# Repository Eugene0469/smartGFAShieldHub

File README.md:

# SmartGFA_hubBoard
This is a design of a sensor hub to connect the hat board to the sensors and rf board.

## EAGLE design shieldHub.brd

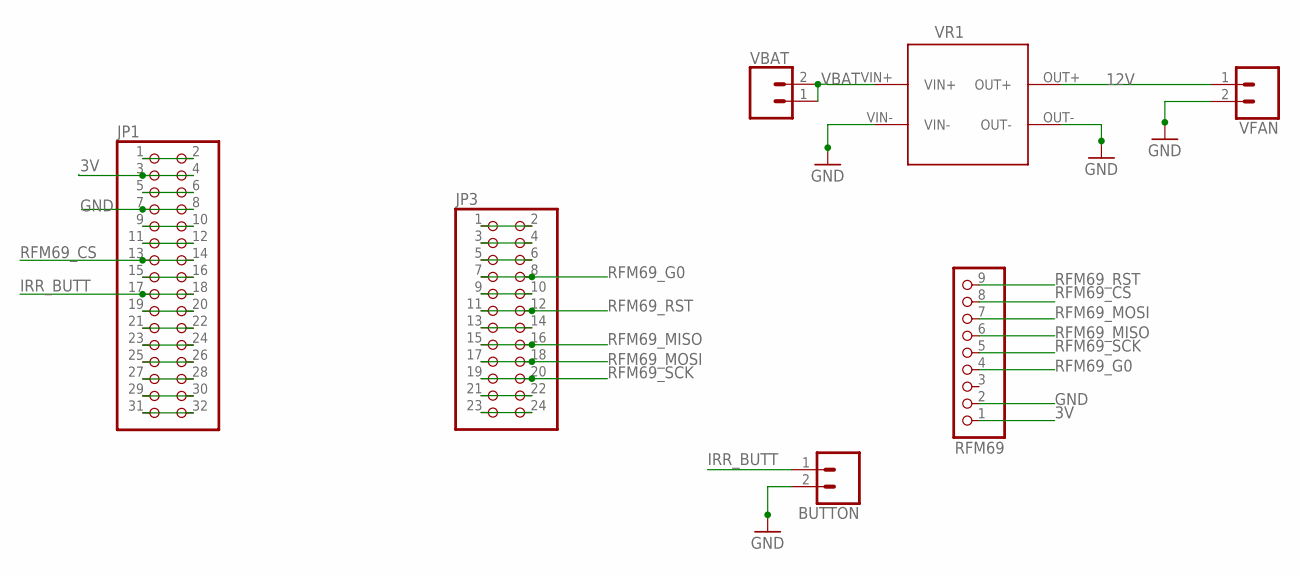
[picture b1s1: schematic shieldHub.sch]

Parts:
BUTTON: CONN_023.5MM_LOCK; SCREWTERMINAL-3.5MM-2_LOCK
JP1: PINHD-2X16; 2X16
JP3: PINHD-2X12; 2X12
RFM69: PINHD-1X9; 1X09-BIG
VBAT: CONN_02; 1X02
VFAN: CONN_023.5MM_LOCK; SCREWTERMINAL-3.5MM-2_LOCK
VR1: MT3608THROUGH_HOLE; MT3608

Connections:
3V: JP1.3, JP1.4, RFM69.1
12V: VFAN.1, VR1.OUT+
GND: BUTTON.2, JP1.7, JP1.8, RFM69.2, VFAN.2, VR1.OUT-, VR1.VIN-
IRR_BUTT: BUTTON.1, JP1.17, JP1.18
unnamed: JP1.1, JP1.2
unnamed: JP1.5, JP1.6
unnamed: JP1.9, JP1.10
unnamed: JP1.11, JP1.12
unnamed: JP3.23, JP3.24
unnamed: JP1.15, JP1.16
unnamed: JP1.19, JP1.20
unnamed: JP1.21, JP1.22
unnamed: JP1.23, JP1.24
unnamed: JP1.25, JP1.26
unnamed: JP3.21, JP3.22
unnamed: JP1.31, JP1.32
unnamed: JP3.13, JP3.14
unnamed: JP3.9, JP3.10
unnamed: JP3.5, JP3.6
unnamed: JP3.3, JP3.4
unnamed: JP3.1, JP3.2
RFM69_CS: JP1.13, JP1.14, RFM69.8
RFM69_G0: JP3.7, JP3.8, RFM69.4
RFM69_MISO: JP3.15, JP3.16, RFM69.6
RFM69_MOSI: JP3.17, JP3.18, RFM69.7
RFM69_RST: JP3.11, JP3.12, RFM69.9
RFM69_SCK: JP3.19, JP3.20, RFM69.5
RX: JP1.27, JP1.28
TX: JP1.29, JP1.30
VBAT: VBAT.1, VBAT.2, VR1.VIN+

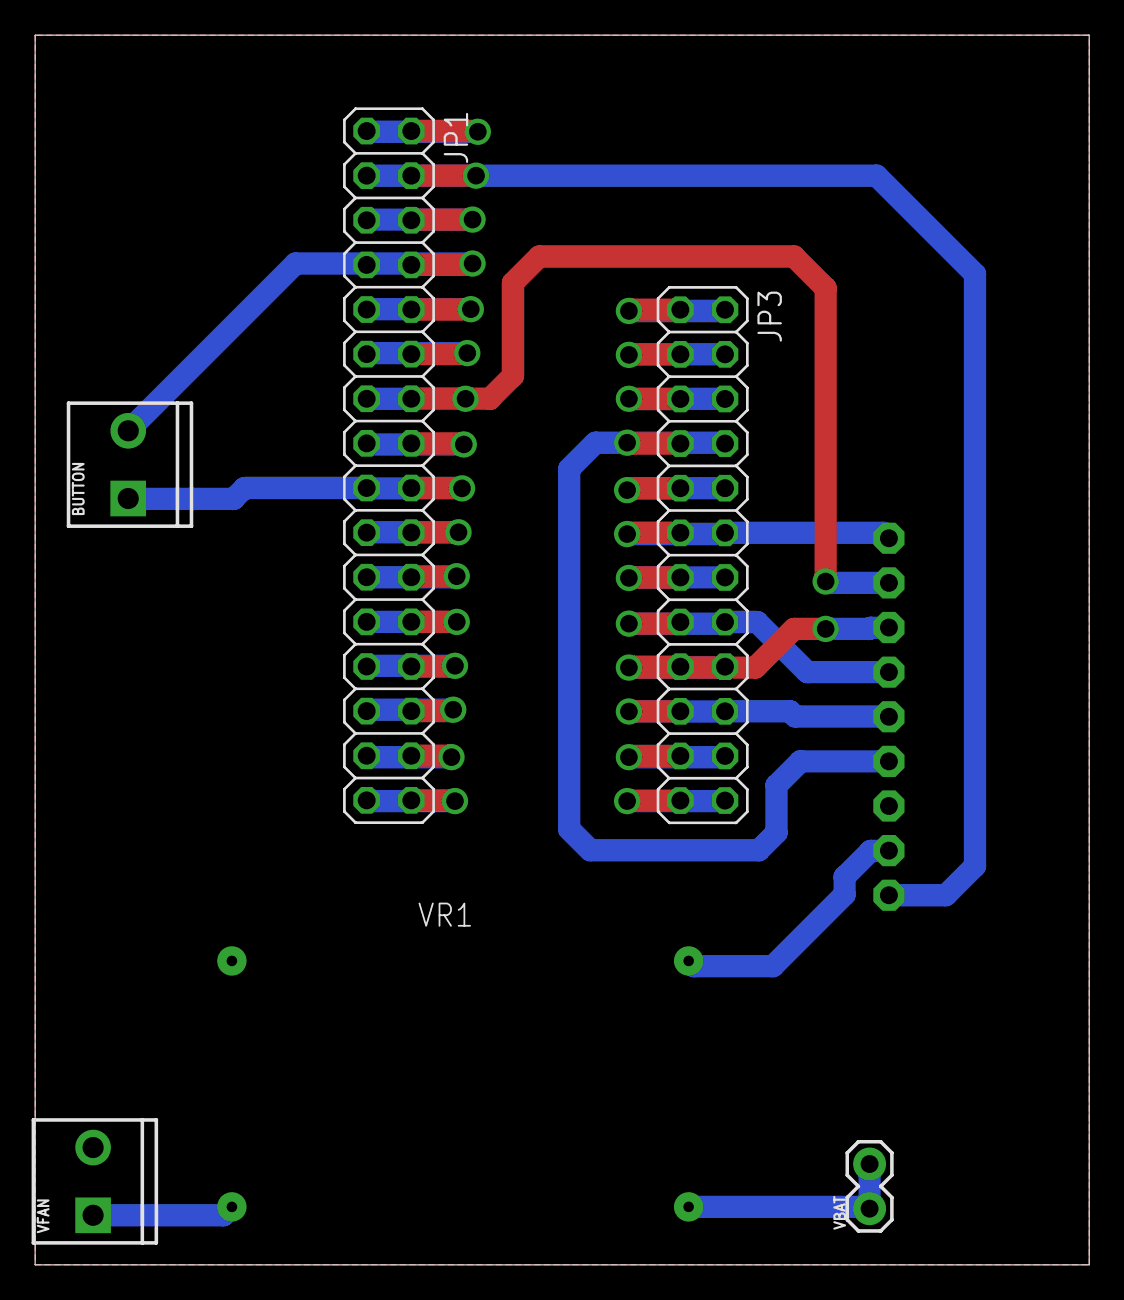
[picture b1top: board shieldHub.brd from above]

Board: 2 copper layers, 60.0 x 70.0 mm, 7 parts (1 on the bottom side), 30 nets.

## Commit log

2020-09-05 Changes sch and brd file names from sensorHub to shieldHub
2020-09-05 Removes sensor connector pins and adds rrm69 header pin
2020-09-05 Adds connector pin for fan power
2020-09-05 Adds connector for button
2020-09-05 Connects rfm69 to boron
2020-09-05 Connects button to boron
2020-09-05 Completes routing of brd file
2020-09-05 Replaces fan power header pin with a connector pin

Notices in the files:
parts and their libraries:
SparkFun-Connectors: Licensing: Creative Commons ShareAlike 4.0 International - https://creativecommons.org/licenses/by-sa/4.0
